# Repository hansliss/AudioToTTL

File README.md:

# AudioToTTL
Audio to TTL adapter stage from my MIDI converter.

This was taken from a schematic for an analogue frequency counter, design 27 in the Elektor book "501 elektroniska byggprojekt" (ISBN 91-86898-00-0) from 1995, a translation from a Dutch book from 1984.

I used this with great success in a 1999 project to convert square wave audio to MIDI using an Atmel AT90S1200, and it turned out to be able to extract information from mixed audio as well. It can probably be used with an Arduino to build frequency counters and similar projects.

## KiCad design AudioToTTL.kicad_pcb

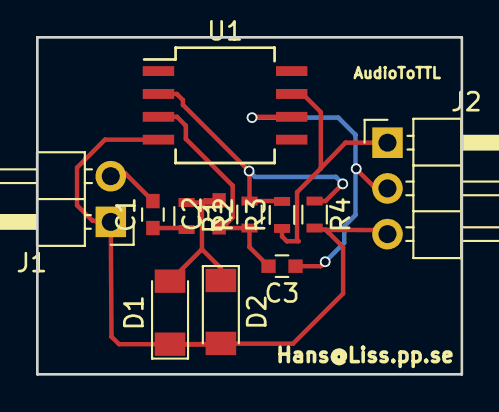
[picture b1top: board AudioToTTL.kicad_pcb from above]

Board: 2 copper layers, 23.6 x 18.7 mm, 12 parts (0 on the bottom side), 8 nets.

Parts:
C1: 22nF; C_0603
C2: 22n; C_0603
C3: 3p3; C_0603
D1, D2: DUS; D_MiniMELF
J1: Audio_in; Pin_Header_Angled_1x02_Pitch2.54mm
J2: TTL_out; Pin_Header_Angled_1x03_Pitch2.54mm
R1: 560k; R_0603
R2: 10M; R_0603
R3, R4: 2k2; R_0603
U1: CA3130; SO-8_5.3x6.2mm_Pitch1.27mm

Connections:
/DOUT: C3.1, J2.2, U1.6
/LINE_IN: C1.2, J1.2
GND: D1.1, D2.2, J1.1, J2.3, R4.2, U1.4
unnamed: C1.1, R1.2
unnamed: C2.1, C3.2, R2.1, U1.3
unnamed: C2.2, D1.2, D2.1, R1.1
unnamed: R2.2, R3.2, R4.1, U1.2
VCC: J2.1, R3.1, U1.7

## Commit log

2018-07-15 Initial import
